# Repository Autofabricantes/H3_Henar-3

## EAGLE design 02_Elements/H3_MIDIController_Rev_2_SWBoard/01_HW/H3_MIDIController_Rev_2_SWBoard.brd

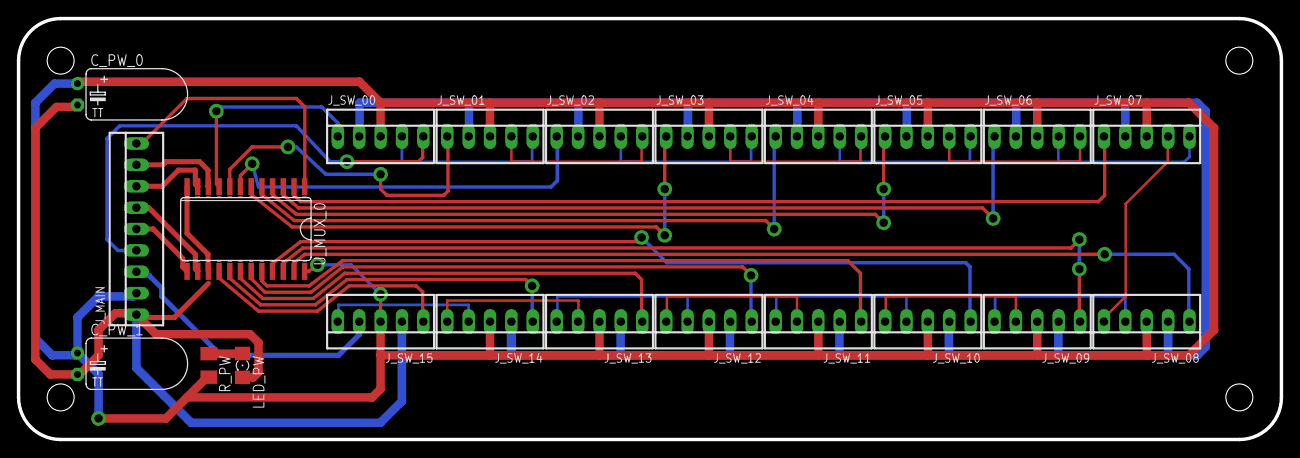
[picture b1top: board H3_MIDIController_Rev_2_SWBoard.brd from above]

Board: 2 copper layers, 150.0 x 50.0 mm, 22 parts (0 on the bottom side), 41 nets.

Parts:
C_PW_0: 10uF; TT2D6L
C_PW_1: 100uF; TT2D6L
J_MAIN: 22-23-2091
J_SW_00, J_SW_01, J_SW_02, J_SW_03, J_SW_04, J_SW_05, J_SW_06, J_SW_07, J_SW_08, J_SW_09, J_SW_10, J_SW_11, J_SW_12, J_SW_13, J_SW_14, J_SW_15: 22-23-2051
LED_PW: 1206
R_PW: 330Ohm; M1206
U_MUX_0: 4067D; SO24W

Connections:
5V: C_PW_0.+, C_PW_1.+, J_MAIN.2, J_SW_00.3, J_SW_01.3, J_SW_02.3, J_SW_03.3, J_SW_04.3, J_SW_05.3, J_SW_06.3, J_SW_07.3, J_SW_08.3, J_SW_09.3, J_SW_10.3, J_SW_11.3, J_SW_12.3, J_SW_13.3, J_SW_14.3, J_SW_15.3, R_PW.2, U_MUX_0.24
GND: C_PW_0.-, C_PW_1.-, J_MAIN.1, J_SW_00.2, J_SW_01.2, J_SW_02.2, J_SW_03.2, J_SW_04.2, J_SW_05.2, J_SW_06.2, J_SW_07.2, J_SW_08.2, J_SW_09.2, J_SW_10.2, J_SW_11.2, J_SW_12.2, J_SW_13.2, J_SW_14.2, J_SW_15.2, LED_PW.C, U_MUX_0.12, U_MUX_0.15
LED_IN: J_MAIN.4, J_SW_00.5
LED_IN1: J_SW_00.4, J_SW_01.5
LED_IN2: J_SW_01.4, J_SW_02.5
LED_IN3: J_SW_02.4, J_SW_03.5
LED_IN4: J_SW_03.4, J_SW_04.5
LED_IN5: J_SW_04.4, J_SW_05.5
LED_IN6: J_SW_05.4, J_SW_06.5
LED_IN7: J_SW_07.4, J_SW_08.5
LED_IN8: J_SW_08.4, J_SW_09.5
LED_IN9: J_SW_09.4, J_SW_10.5
LED_IN10: J_SW_10.4, J_SW_11.5
LED_IN11: J_SW_11.4, J_SW_12.5
LED_IN12: J_SW_12.4, J_SW_13.5
LED_IN13: J_SW_13.4, J_SW_14.5
LED_IN14: J_SW_14.4, J_SW_15.5
LED_OUT: J_MAIN.3, J_SW_15.4
MUX_0_OUT: J_MAIN.9, U_MUX_0.1
MUX_A: J_MAIN.8, U_MUX_0.10
MUX_B: J_MAIN.7, U_MUX_0.11
MUX_C: J_MAIN.6, U_MUX_0.14
MUX_D: J_MAIN.5, U_MUX_0.13
unnamed: J_SW_06.4, J_SW_07.5
unnamed: LED_PW.A, R_PW.1
SW_00: J_SW_00.1, U_MUX_0.9
SW_01: J_SW_01.1, U_MUX_0.8
SW_02: J_SW_02.1, U_MUX_0.7
SW_03: J_SW_03.1, U_MUX_0.6
SW_04: J_SW_04.1, U_MUX_0.5
SW_05: J_SW_05.1, U_MUX_0.4
SW_06: J_SW_06.1, U_MUX_0.3
SW_07: J_SW_07.1, U_MUX_0.2
SW_08: J_SW_08.1, U_MUX_0.23
SW_09: J_SW_09.1, U_MUX_0.22
SW_10: J_SW_10.1, U_MUX_0.21
SW_11: J_SW_11.1, U_MUX_0.20
SW_12: J_SW_12.1, U_MUX_0.19
SW_13: J_SW_13.1, U_MUX_0.18
SW_14: J_SW_14.1, U_MUX_0.17
SW_15: J_SW_15.1, U_MUX_0.16

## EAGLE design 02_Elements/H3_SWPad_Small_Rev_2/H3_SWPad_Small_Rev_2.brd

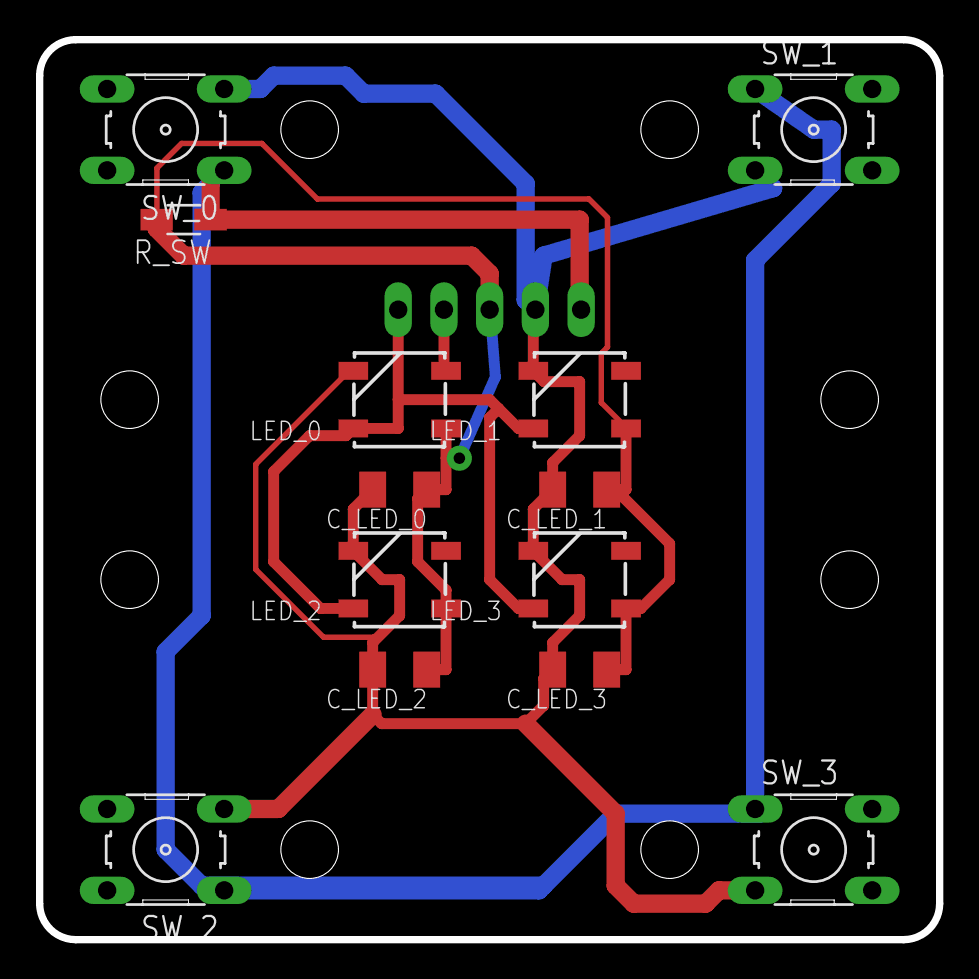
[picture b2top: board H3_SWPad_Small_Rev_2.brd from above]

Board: 2 copper layers, 50.0 x 50.0 mm, 14 parts (1 on the bottom side), 5 nets.

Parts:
C_LED_0, C_LED_1, C_LED_2, C_LED_3: 10uF; C1206K
J_MAIN: 22-05-7058-05; 7395-05
LED_0, LED_1, LED_2, LED_3: WS2812B
R_SW: 10kOhm; R1206W
SW_0, SW_1, SW_2, SW_3: B3F-10XX

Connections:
5V: C_LED_0.1, C_LED_1.1, C_LED_2.1, C_LED_3.1, J_MAIN.3, LED_0.1, LED_1.1, LED_2.1, LED_3.1, R_SW.2
GND: C_LED_0.2, C_LED_1.2, C_LED_2.2, C_LED_3.2, J_MAIN.2, LED_0.3, LED_1.3, LED_2.3, LED_3.3, SW_0.3, SW_1.3, SW_2.3, SW_3.3
LED_IN: J_MAIN.5, LED_0.4, LED_1.4, LED_2.4, LED_3.4
LED_OUT: J_MAIN.4, LED_0.2
SW: J_MAIN.1, R_SW.1, SW_0.1, SW_1.1, SW_2.1, SW_3.1

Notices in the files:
parts and their libraries:
SparkFun-LED: Licensing: Creative Commons ShareAlike 4.0 International - https://creativecommons.org/licenses/by-sa/4.0
